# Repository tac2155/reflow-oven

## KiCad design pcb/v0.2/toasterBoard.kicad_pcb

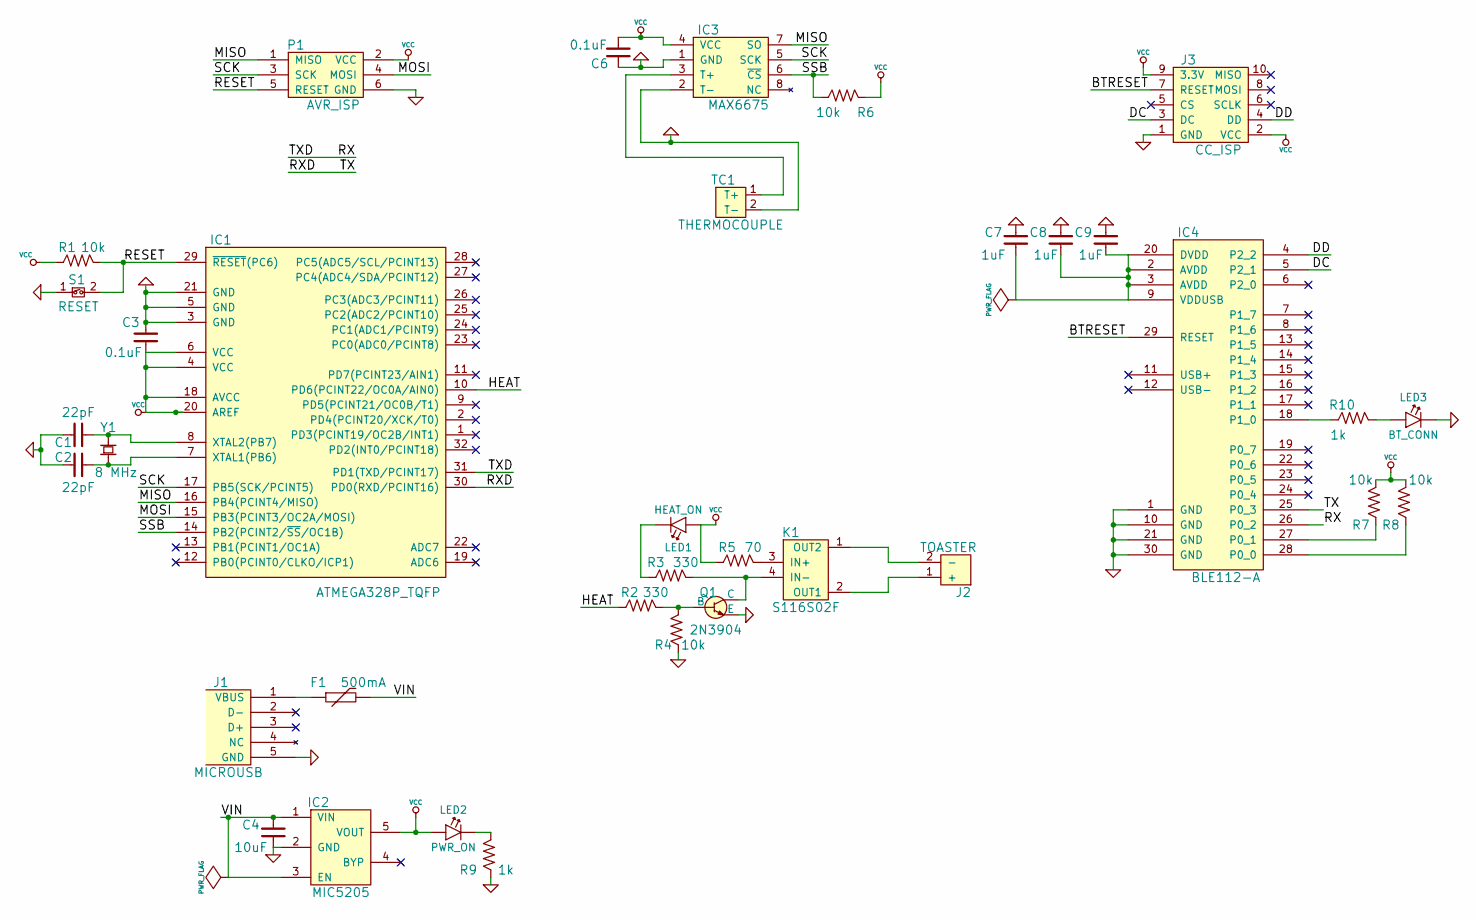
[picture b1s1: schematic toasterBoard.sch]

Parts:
C1, C2: 22pF
C3, C6: 0.1uF
C4: 10uF
C7, C8, C9: 1uF
F1: 500mA
IC1: ATMEGA328P_TQFP
IC2: MIC5205
IC3: MAX6675
IC4: BLE112-A
J1: MICROUSB
J2: TOASTER
J3: CC_ISP
K1: S116S02F
LED1: HEAT_ON
LED2: PWR_ON
LED3: BT_CONN
P1: AVR_ISP
Q1: 2N3904
R1, R4, R6, R7, R8: 10k
R2, R3: 330
R5: 70
R9, R10: 1k
S1: RESET
TC1: THERMOCOUPLE
Y1: 8 MHz

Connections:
/BTRESET: IC4.29 (RESET), J3.7 (RESET)
/DC: IC4.5 (P2_1), J3.3 (DC)
/DD: IC4.4 (P2_2), J3.4 (DD)
/HEAT: IC1.10 (PD6(PCINT22/OC0A/AIN0)), R2.1
/MISO: IC1.16 (PB4(PCINT4/MISO)), IC3.7 (SO), P1.1 (MISO)
/MOSI: IC1.15 (PB3(PCINT3/OC2A/MOSI)), P1.4 (MOSI)
/RESET: IC1.29 (~RESET~(PC6)), P1.5 (RESET), R1.2, S1.2
/RX: IC1.31 (PD1(TXD/PCINT17)), IC4.26 (P0_2)
/RXD: IC1.30 (PD0(RXD/PCINT16)), IC4.25 (P0_3)
/SCK: IC1.17 (PB5(SCK/PCINT5)), IC3.5 (SCK), P1.3 (SCK)
/SSB: IC1.14 (PB2(PCINT2/~SS~/OC1B)), IC3.6 (~CS~), R6.1
/VIN: C4.2, F1.2, IC2.1 (VIN), IC2.3 (EN)
GND: C1.1, C2.1, C3.2, C4.1, C6.1, C7.2, C8.2, C9.2, IC1.3 (GND), IC1.5 (GND), IC1.21 (GND), IC2.2 (GND), IC3.1 (GND), IC3.2 (T-), IC4.1 (GND), IC4.10 (GND), IC4.21 (GND), IC4.30 (GND), J1.5 (GND), J3.1 (GND), LED3.1 (C), P1.6 (GND), Q1.1 (E), R4.1, R9.1, S1.1, TC1.2 (T-)
unnamed: IC3.3 (T+), TC1.1 (T+)
unnamed: LED1.1 (C), R3.1
unnamed: LED2.1 (C), R9.2
unnamed: LED3.2 (A), R10.2
unnamed: IC4.18 (P1_0), R10.1
unnamed: J2.1 (+), K1.2 (OUT1)
unnamed: K1.4 (IN-), Q1.3 (C), R3.2
unnamed: J2.2 (-), K1.1 (OUT2)
unnamed: IC4.27 (P0_1), R7.1
unnamed: IC4.28 (P0_0), R8.1
unnamed: F1.1, J1.1 (VBUS)
unnamed: C7.1, C8.1, C9.1, IC4.2 (AVDD), IC4.3 (AVDD), IC4.9 (VDDUSB), IC4.20 (DVDD)
unnamed: C1.2, IC1.8 (XTAL2(PB7)), Y1.2
unnamed: C2.2, IC1.7 (XTAL1(PB6)), Y1.1
unnamed: Q1.2 (B), R2.2, R4.2
unnamed: K1.3 (IN+), R5.2
VCC: C3.1, C6.2, IC1.4 (VCC), IC1.6 (VCC), IC1.18 (AVCC), IC1.20 (AREF), IC2.5 (VOUT), IC3.4 (VCC), J3.2 (VCC), J3.9 (3.3V), LED1.2 (A), LED2.2 (A), P1.2 (VCC), R1.1, R5.1, R6.2, R7.2, R8.2

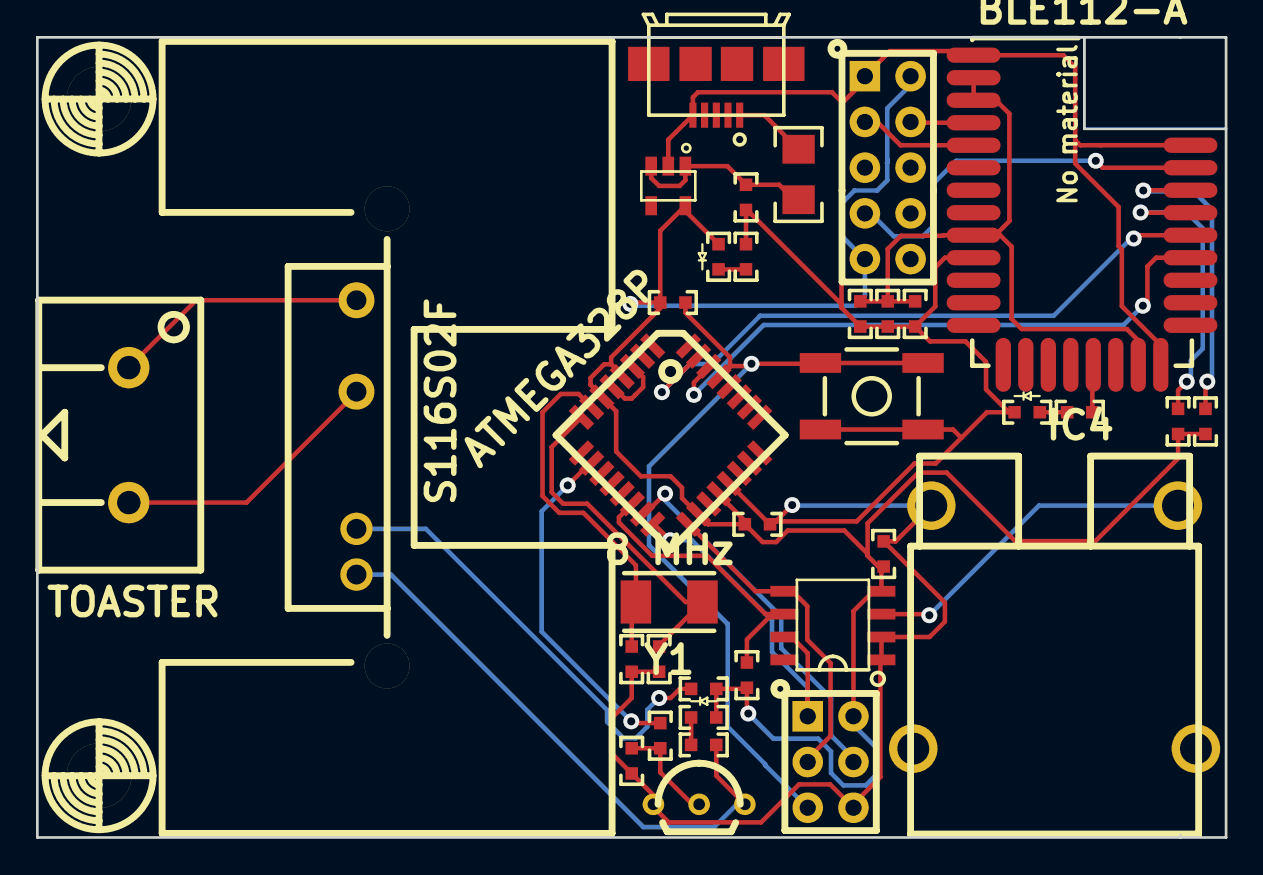
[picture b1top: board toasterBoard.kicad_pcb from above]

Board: 2 copper layers, 66.0 x 44.4 mm, 37 parts (0 on the bottom side), 30 nets.

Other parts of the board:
M3, M3#2: VAL**; M3

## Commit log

2013-07-05 first repo
2013-07-09 working on uart
2013-07-15 new pcb layout
2013-07-15 small changes
2013-07-16 new pbc layout
2013-07-16 working on firmware
2013-07-16 small changes to board
